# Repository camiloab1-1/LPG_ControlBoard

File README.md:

View this project on [CADLAB.io](https://cadlab.io/project/28271). 

# LPG_ControlBoard
This is a Master's Degree project, for the UC3M (Universidad Carlos III Madrid)

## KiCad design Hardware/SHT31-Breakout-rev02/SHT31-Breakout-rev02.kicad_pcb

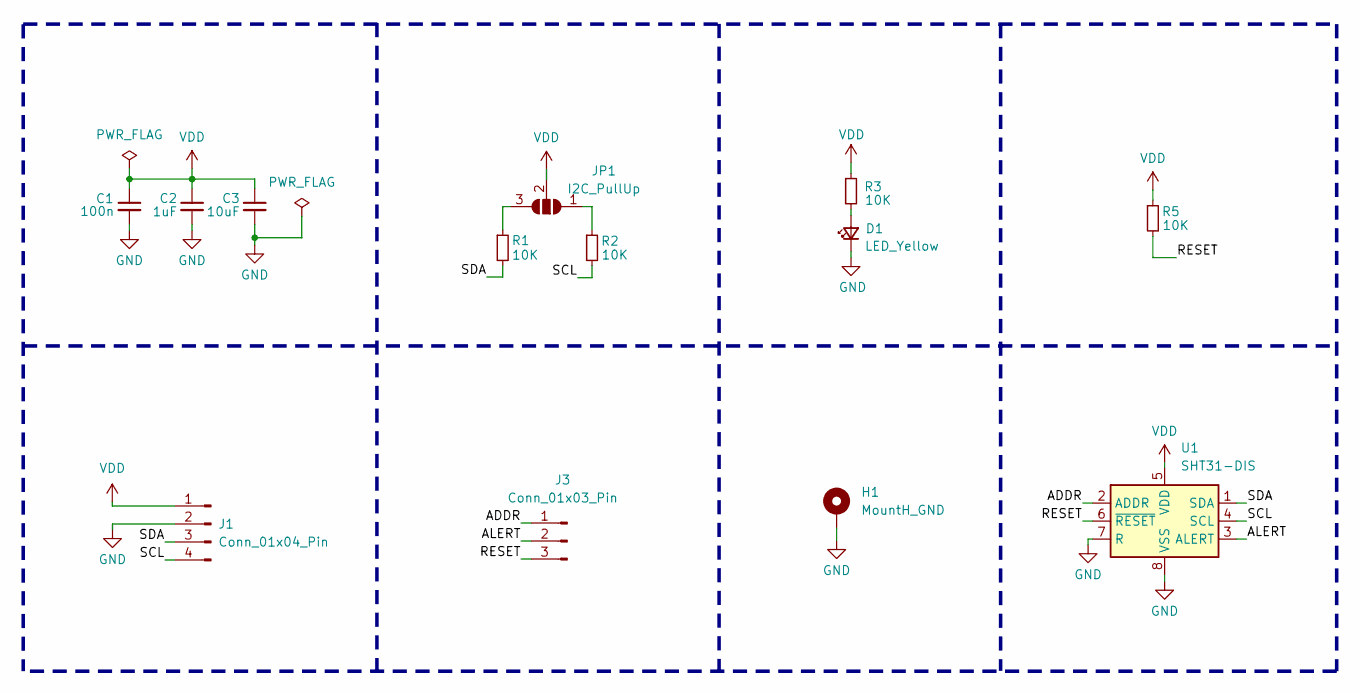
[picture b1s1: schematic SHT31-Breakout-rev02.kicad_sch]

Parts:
C1: 100n; C_0402_1005Metric_Pad0.74x0.62mm_HandSolder
C2: 1uF; C_0402_1005Metric_Pad0.74x0.62mm_HandSolder
C3: 10uF; C_0402_1005Metric_Pad0.74x0.62mm_HandSolder
D1: LED_Yellow; LED_0402_1005Metric_Pad0.77x0.64mm_HandSolder
H1: MountH_GND; MountingHole_4mm_Pad_TopBottom
J1: Conn_01x04_Pin; PinHeader_1x04_P2.54mm_Vertical
J3: Conn_01x03_Pin; PinHeader_1x03_P2.54mm_Vertical
JP1: I2C_PullUp; SolderJumper-3_P1.3mm_Open_RoundedPad1.0x1.5mm_NumberLabels
R1, R2, R3, R5: 10K; R_0402_1005Metric_Pad0.72x0.64mm_HandSolder
U1: SHT31-DIS; Sensirion_DFN-8-1EP_2.5x2.5mm_P0.5mm_EP1.1x1.7mm

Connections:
/ADDR: J3.1, U1.2 (ADDR)
/ALERT: J3.2, U1.3 (ALERT)
/RESET: J3.3, R5.2, U1.6 (~RESET)
/SCL: J1.4, R2.2, U1.4 (SCL)
/SDA: J1.3, R1.2, U1.1 (SDA)
GND: C1.2, C2.2, C3.2, D1.1 (K), H1.1, J1.2, U1.7 (R), U1.8 (VSS), U1.9 (VSS)
unnamed: D1.2 (A), R3.2
unnamed: JP1.1 (A), R2.1
unnamed: JP1.3 (B), R1.1
VDD: C1.1, C2.1, C3.1, J1.1, JP1.2 (C), R3.1, R5.1, U1.5 (VDD)

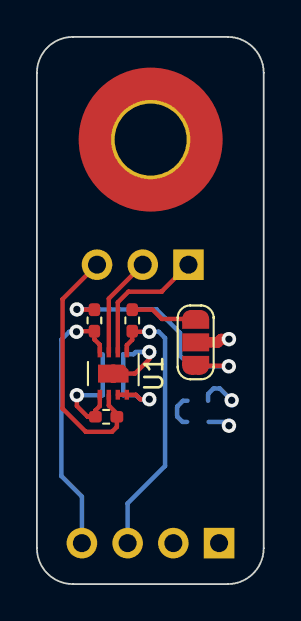
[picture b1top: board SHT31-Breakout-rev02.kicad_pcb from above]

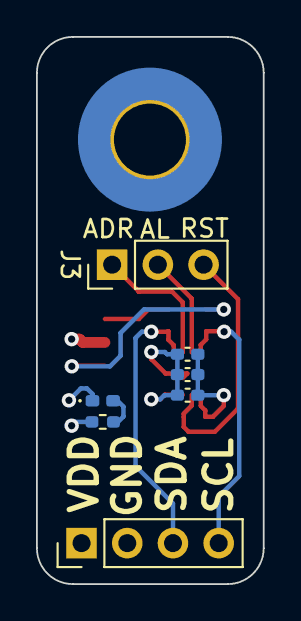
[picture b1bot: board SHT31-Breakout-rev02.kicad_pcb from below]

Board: 4 copper layers, 12.6 x 30.4 mm, 13 parts (7 on the bottom side), 10 nets.

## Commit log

2024-07-12 Backlink to CADLAB.io has been added.
